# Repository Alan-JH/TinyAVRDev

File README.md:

# TinyAVRDev
 Dev boards for various Attiny 0/1/2 series AVR microcontrollers

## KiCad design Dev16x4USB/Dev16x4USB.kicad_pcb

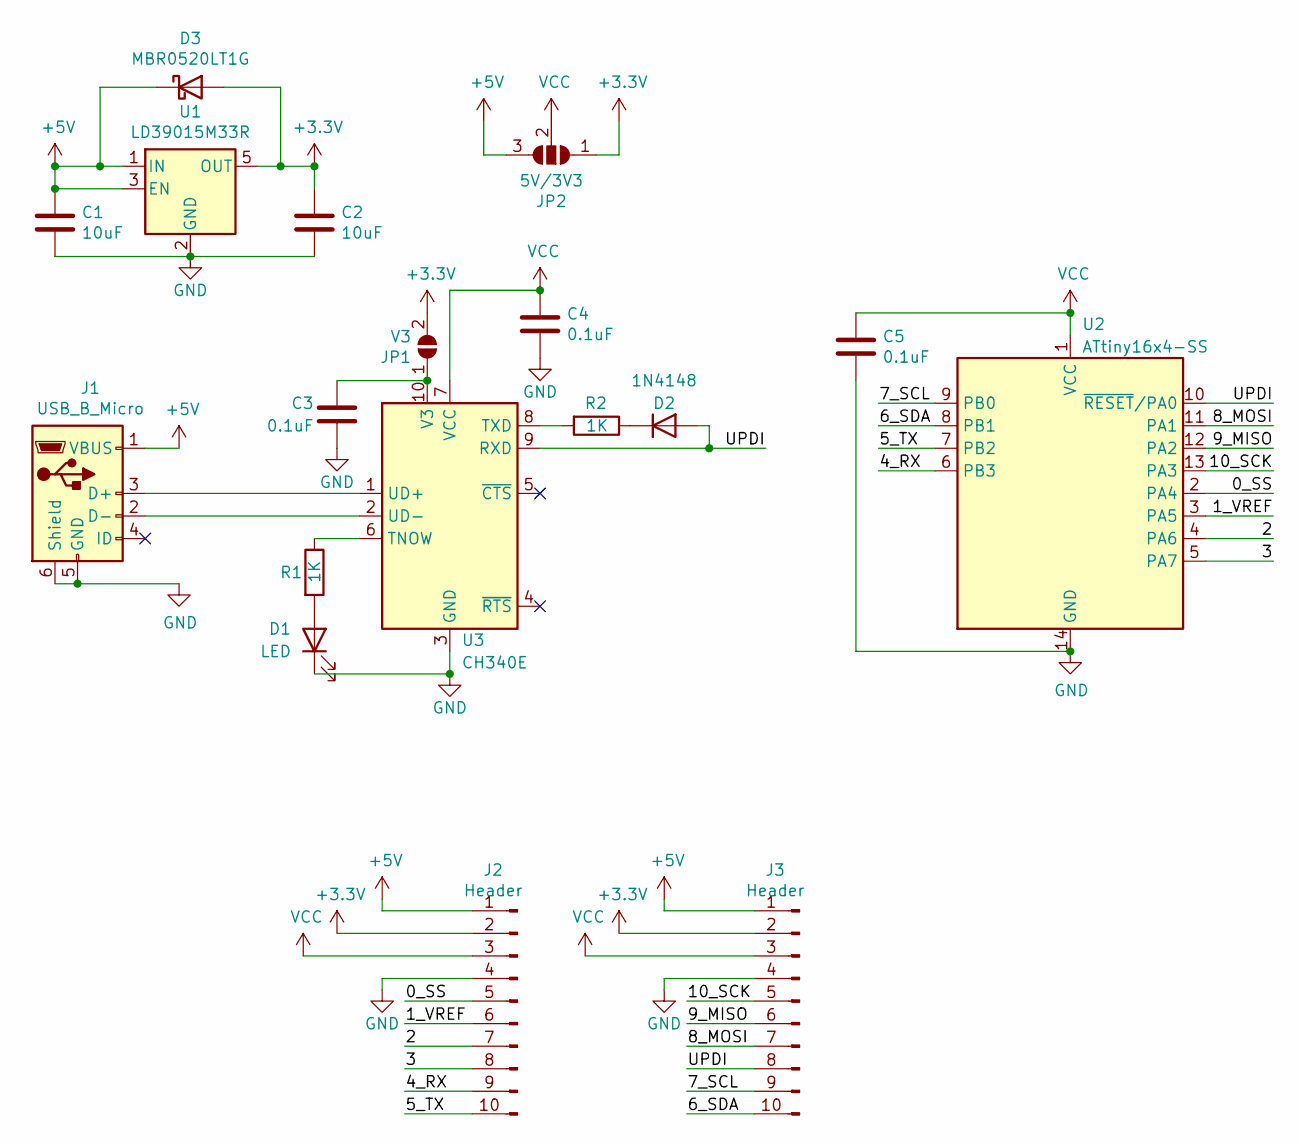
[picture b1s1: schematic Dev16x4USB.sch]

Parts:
C1, C2: 10uF; C_0603_1608Metric
C3, C4, C5: 0.1uF; C_0603_1608Metric
D1: LED; LED_0805_2012Metric
D2: 1N4148; D_SOD-323
D3: MBR0520LT1G; D_SOD-123
J1: USB_B_Micro; AdafruitMicroB
J2, J3: Header; PinHeader_1x10_P2.54mm_Vertical
JP1: V3; SolderJumper-2_P1.3mm_Open_Pad1.0x1.5mm
JP2: 5V/3V3; SolderJumper-3_P1.3mm_Open_Pad1.0x1.5mm
R1, R2: 1K; R_0805_2012Metric
U1: LD39015M33R; SOT-23-5
U2: ATtiny16x4-SS; SOIC-14_3.9x8.7mm_P1.27mm
U3: CH340E; MSOP-10_3x3mm_P0.5mm

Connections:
+3V3: C2.1, D3.2 (A), J2.2, J3.2, JP1.2 (B), JP2.1 (A), U1.5 (OUT); also elsewhere on the board
+5V: C1.1, D3.1 (K), J1.1 (VBUS), J2.1, J3.1, JP2.3 (B), U1.1 (IN), U1.3 (EN); also elsewhere on the board
/0_SS: J2.5, U2.2 (PA4)
/1_VREF: J2.6, U2.3 (PA5)
/2: J2.7, U2.4 (PA6)
/3: J2.8, U2.5 (PA7)
/4_RX: J2.9, U2.6 (PB3)
/5_TX: J2.10, U2.7 (PB2)
/6_SDA: J3.10, U2.8 (PB1)
/7_SCL: J3.9, U2.9 (PB0)
/8_MOSI: J3.7, U2.11 (PA1)
/9_MISO: J3.6, U2.12 (PA2)
/10_SCK: J3.5, U2.13 (PA3)
/UPDI: D2.2 (A), J3.8, U2.10 (~RESET~/PA0), U3.9 (RXD)
GND: C1.2, C2.2, C3.2, C4.2, C5.2, D1.1 (K), J1.5 (GND), J1.6 (Shield), J2.4, J3.4, U1.2 (GND), U2.14 (GND), U3.3 (GND)
unnamed: C3.1, JP1.1 (A), U3.10 (V3)
unnamed: D1.2 (A), R1.2
unnamed: D2.1 (K), R2.1
unnamed: J1.2 (D-), U3.2 (UD-)
unnamed: J1.3 (D+), U3.1 (UD+)
unnamed: R1.1, U3.6 (TNOW)
unnamed: R2.2, U3.8 (TXD)
VCC: C4.1, C5.1, J2.3, J3.3, JP2.2 (C), U2.1 (VCC), U3.7 (VCC); also elsewhere on the board

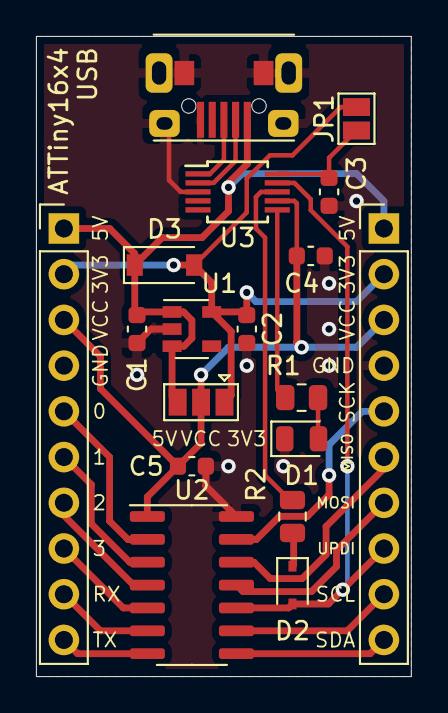
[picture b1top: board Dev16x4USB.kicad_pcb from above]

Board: 2 copper layers, 20.8 x 35.6 mm, 18 parts (0 on the bottom side), 23 nets.

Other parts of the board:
VCC: 5V/3V3; SolderJumper-3_P1.3mm_Open_Pad1.0x1.5mm

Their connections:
+3V3: VCC.1; also elsewhere on the board
+5V: VCC.3; also elsewhere on the board
VCC: VCC.2; also elsewhere on the board

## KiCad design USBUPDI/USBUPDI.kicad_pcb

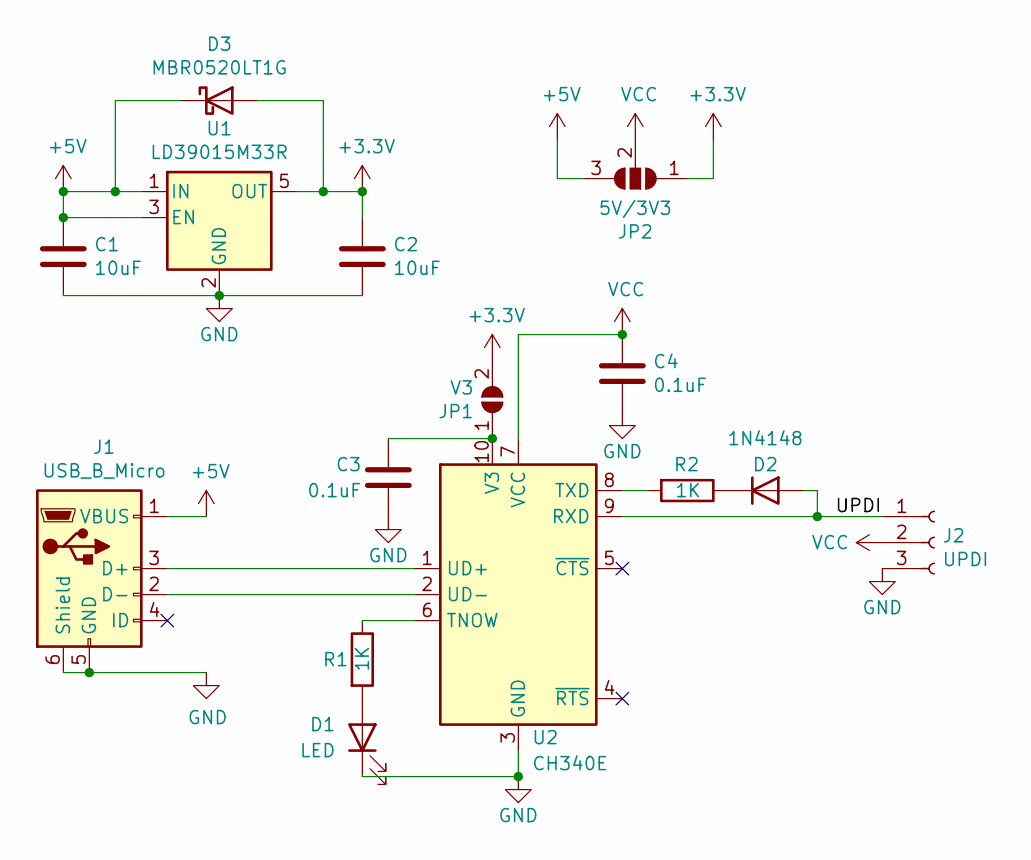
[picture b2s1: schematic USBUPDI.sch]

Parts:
C1, C2: 10uF; C_0603_1608Metric
C3, C4: 0.1uF; C_0603_1608Metric
D1: LED; LED_0805_2012Metric
D2: 1N4148; D_SOD-323
D3: MBR0520LT1G; D_SOD-123
J1: USB_B_Micro; AdafruitMicroB
J2: UPDI; PinSocket_1x03_P2.54mm_Horizontal
JP1: V3; SolderJumper-2_P1.3mm_Open_Pad1.0x1.5mm
JP2: 5V/3V3; SolderJumper-3_P1.3mm_Open_Pad1.0x1.5mm
R1, R2: 1K; R_0805_2012Metric
U1: LD39015M33R; SOT-23-5
U2: CH340E; MSOP-10_3x3mm_P0.5mm

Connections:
+3V3: C2.1, D3.2 (A), JP1.2 (B), JP2.1 (A), U1.5 (OUT); also elsewhere on the board
+5V: C1.1, D3.1 (K), J1.1 (VBUS), JP2.3 (B), U1.1 (IN), U1.3 (EN); also elsewhere on the board
/UPDI: D2.2 (A), J2.1, U2.9 (RXD)
GND: C1.2, C2.2, C3.2, C4.2, D1.1 (K), J1.5 (GND), J1.6 (Shield), J2.3, U1.2 (GND), U2.3 (GND)
unnamed: C3.1, JP1.1 (A), U2.10 (V3)
unnamed: D1.2 (A), R1.2
unnamed: D2.1 (K), R2.1
unnamed: J1.2 (D-), U2.2 (UD-)
unnamed: J1.3 (D+), U2.1 (UD+)
unnamed: R1.1, U2.6 (TNOW)
unnamed: R2.2, U2.8 (TXD)
VCC: C4.1, J2.2, JP2.2 (C), U2.7 (VCC); also elsewhere on the board

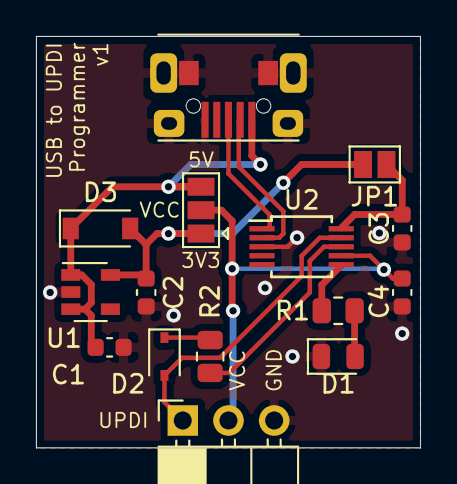
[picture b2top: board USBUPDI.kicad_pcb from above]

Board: 2 copper layers, 21.3 x 22.9 mm, 15 parts (0 on the bottom side), 12 nets.

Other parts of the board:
VCC: 5V/3V3; SolderJumper-3_P1.3mm_Open_Pad1.0x1.5mm

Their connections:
+3V3: VCC.1; also elsewhere on the board
+5V: VCC.3; also elsewhere on the board
VCC: VCC.2; also elsewhere on the board

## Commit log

2022-01-17 16x4, no routing yet
2022-01-17 Finish v1 16x4 USB
2022-01-17 Add USB to UPDI Programmer
